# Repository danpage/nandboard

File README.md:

# NANDboard: hands-on Boolean algebra

<!--- -------------------------------------------------------------------- --->

## History

Starting in the 2012/13 academic year, the
[Computer Science Department](http://www.cs.bris.ac.uk)
at the
[University of Bristol](http://www.bris.ac.uk)
changed how the Undergraduate-level, 1st year (or "freshman") Computer
Architecture unit was delivered.  Although it *always* had a practical
emphasis, there was a view it should be even more hands-on.
There were various motivations, included the fact that
a) by doing so the topic could be more engaging,
   but also
b) it seeds an ethos and skills that are of general use: for example,
   it could mean students participate more actively in
   [maker-like](http://en.wikipedia.org/wiki/Maker_culture),
   hardware-based (versus software-only) projects.

The NANDboard, whose original concept and design was due to
[Simon Hollis](https://github.com/simonhollis),
was among various innovations introduced; Simon left at the end of the
2014/15 academic year, ~~prompting~~ forcing me to learn the basics of
PCB design and subsequently revise his initial NANDboard version.

<!--- -------------------------------------------------------------------- --->

## Concept

Although fundamentally important in Computer Science,
[Boolean algebra](http://en.wikipedia.org/wiki/Boolean_algebra)
is a notoriously dry topic.  The problem is exacerbated when hands-on 
experience amounts to solving paper-and-pencil exercises; the typical
result is for students to be increasingly uninterested and disengaged.
The underlying causes are varied, and differ from student to student.
However, anecdotally at least, the following are common:

- There is a disconnection between theory and practice, in the sense
  it is unclear how Boolean algebra directly relates to intuitively 
  useful forms of computation;
  this typically leads to students disengaging,
  based on the view that said theory has no practical use (to them).
- Paper-and-pencil exercises are of a necessarily small scale, which
  can mean 
  [toy problems](http://en.wikipedia.org/wiki/Toy_problem)
  dominate; 
  this typically leads to students disengaging, e.g., because they
  can easily solve said problems so avoid any deeper investigation
  of physical constraints and properties, and unusual designs
  (e.g., a [C-element](https://en.wikipedia.org/wiki/C-element)).
- In part due to the wealth of resources available, modern students 
  are used to and excited by the immediacy of software development;
  this is often direct motivation for studying Computer Science in 
  the first place, with Boolean algebra feeling like a regression 
  towards Mathematics (which, for some, is less popular).

Put another way, this approach is similar, by analogy, to learning
[C](http://en.wikipedia.org/wiki/C_(programming_language))
by studying the language and 
["hello world"](https://en.wikipedia.org/wiki/"Hello,_World!"_program)
style programs *without* ever actually compiling and executing them.

An obvious alternative is to connect theory and practice directly, by
supporting genuinely hands-on, experimental tasks.  One way to do so
might be to equip each student with a breadboard and some
[7400 series](https://en.wikipedia.org/wiki/List_of_7400_series_integrated_circuits)
ICs.  However, for us at least, this presented some problems:
a) large cohort sizes
   (of say 200+ students)
   make the logistics involved quite challenging,
b) said cohorts are typically unfamiliar with, and sometimes have an
   outright dislike for electronics.
The NANDboard attempts to manage these problems.  Conceptually, it is 
just a USB-powered breadboard pre-populated with NAND gates: it could
be viewed as a form of NAND-only
[PLA](http://en.wikipedia.org/wiki/Programmable_logic_array),
where implementation of a Boolean expression (cf. programming the PLA)
amounts to connecting pin headers (i.e., the gate inputs and outputs)
using jumper wire.  There are, of course, some gratuitous
[blinkenlights](http://en.wikipedia.org/wiki/Blinkenlights)
to visualise the inputs and outputs.

<!--- -------------------------------------------------------------------- --->

## Design

Motivated in part by observing how students use them, the NANDboard 
design has gone through several revisions as is illustrated below:

Revision | Image                                                                             | Design                                                                             |
:------: | :-------------------------------------------------------------------------------: | :--------------------------------------------------------------------------------: |
B        |  |                                                                                    |
C        |  |                                                                                    |
D        |  | [files](./rev_d), [schematic](./rev_d/README.pdf), [user guide](./rev_d/README.md) |
F        |  | [files](./rev_f), [schematic](./rev_f/README.pdf), [user guide](./rev_f/README.md) |

<!--- -------------------------------------------------------------------- --->

## Acknowledgements

Later revisions 
(e.g., rev. F) 
were designed and manufactured with generous support from 
[Elliptic Systems](https://elliptic-systems.com).

<!--- -------------------------------------------------------------------- --->

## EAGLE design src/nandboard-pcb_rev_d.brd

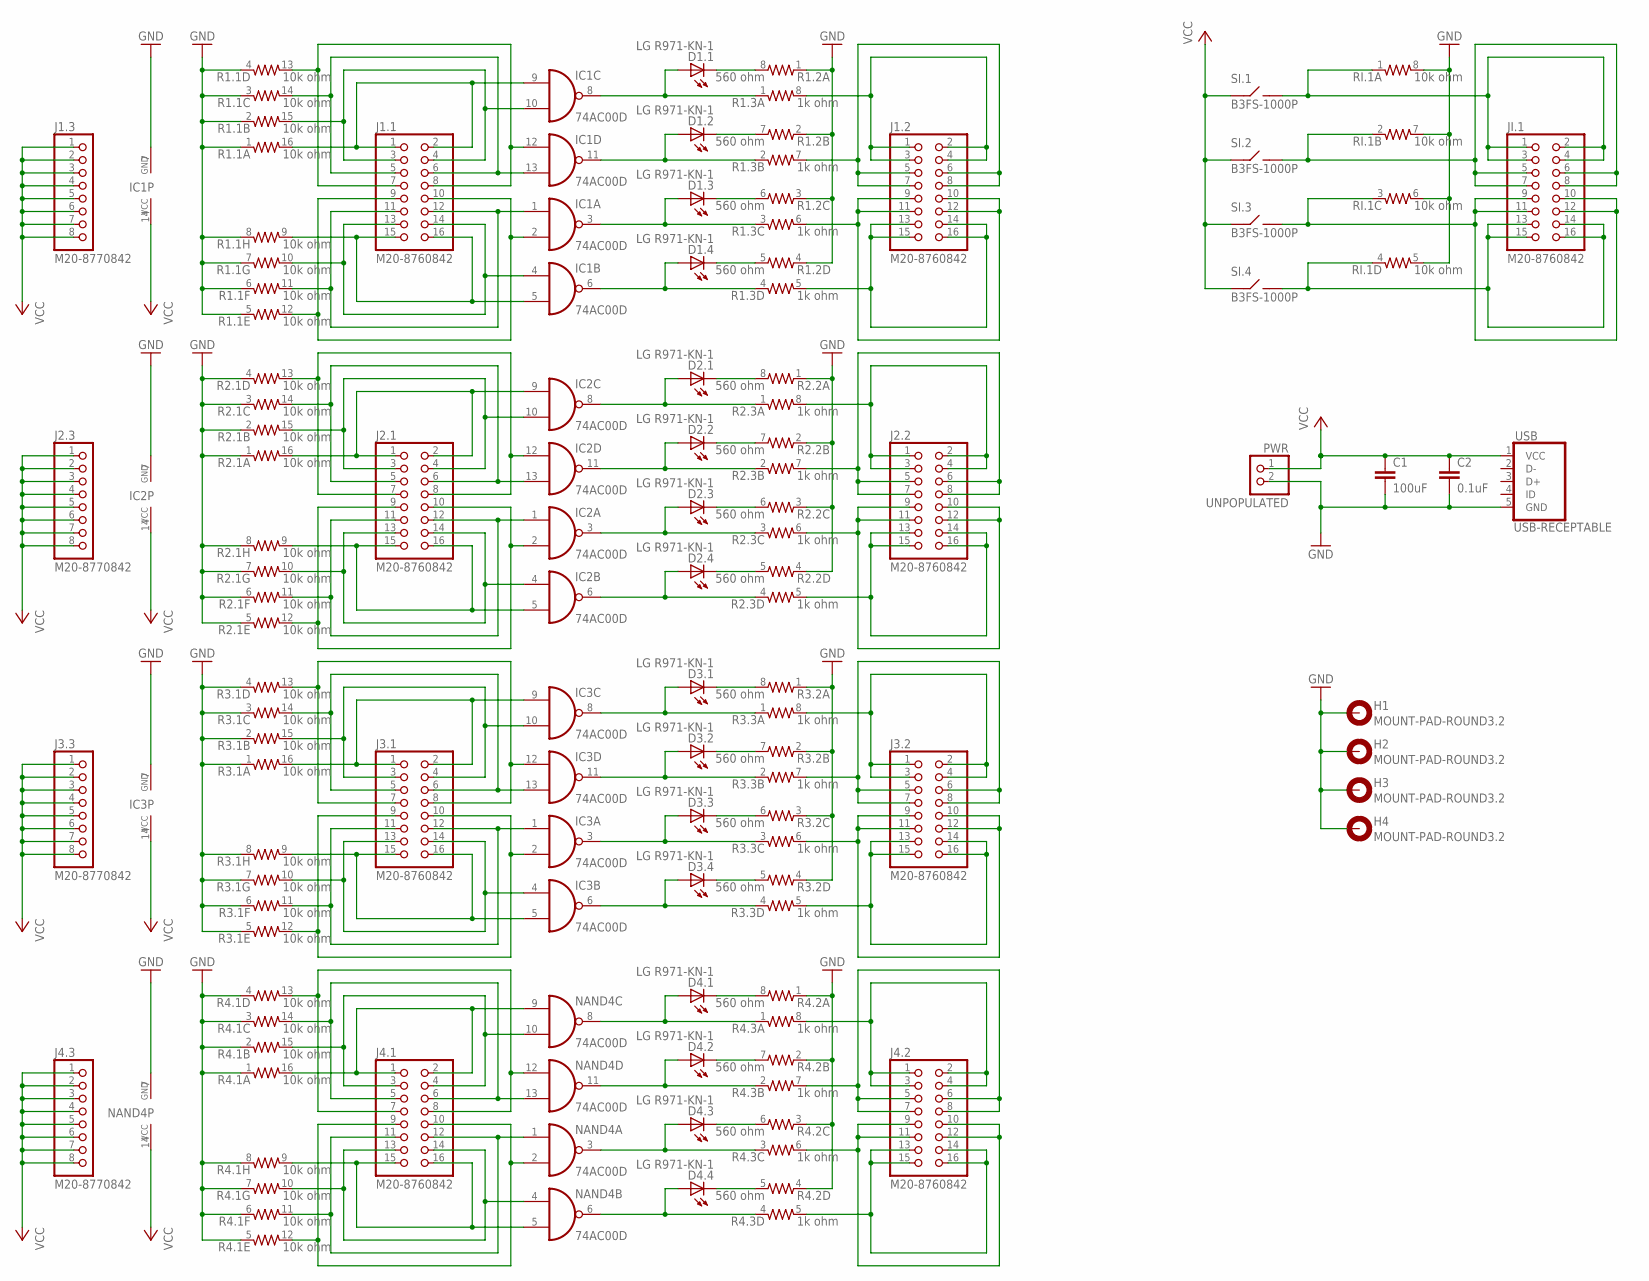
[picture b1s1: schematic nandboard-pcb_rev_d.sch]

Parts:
C1: 100uF; C1210
C2: 0.1uF; C0805
D1.1, D1.2, D1.3, D1.4, D2.1, D2.2, D2.3, D2.4, D3.1, D3.2, D3.3, D3.4, D4.1, D4.2, D4.3, D4.4: LG R971-KN-1; CHIPLED_0805
H1, H2, H3, H4: MOUNT-PAD-ROUND3.2; 3,2-PAD
IC1, IC2, IC3: 74AC00D; SO14
J1.1, J1.2, J2.1, J2.2, J3.1, J3.2, J4.1, J4.2: M20-8760842; 2X08_SMT
J1.3, J2.3, J3.3, J4.3: M20-8770842; 1X08_SMT
JI.1: M20-8760842; 2X08_SMT
NAND4: 74AC00D; SO14
PWR: UNPOPULATED; 1X02
R1.1, R2.1, R3.1, R4.1: 10k ohm; 742-16
R1.2, R2.2, R3.2, R4.2: 560 ohm; 742-8
R1.3, R2.3, R3.3, R4.3: 1k ohm; 742-8
RI.1: 10k ohm; 742-8
SI.1, SI.2, SI.3, SI.4: B3FS-1000P; B3FS-1000
USB: USB-RECEPTABLE; FCI-10103594-0001LF

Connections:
GND: C1.2, C2.2, H1.B3,2, H2.B3,2, H3.B3,2, H4.B3,2, IC1.7 (GND), IC2.7 (GND), IC3.7 (GND), NAND4.7 (GND), PWR.2, R1.1.1, R1.1.2 (1), R1.1.3 (1), R1.1.4 (1), R1.1.5 (1), R1.1.6 (1), R1.1.7 (1), R1.1.8 (1), R1.2.1, R1.2.2 (1), R1.2.3 (1), R1.2.4 (1), R2.1.1, R2.1.2 (1), R2.1.3 (1), R2.1.4 (1), R2.1.5 (1), R2.1.6 (1), R2.1.7 (1), R2.1.8 (1), R2.2.1, R2.2.2 (1), R2.2.3 (1), R2.2.4 (1), R3.1.1, R3.1.2 (1), R3.1.3 (1), R3.1.4 (1), R3.1.5 (1), R3.1.6 (1), R3.1.7 (1), R3.1.8 (1), R3.2.1, R3.2.2 (1), R3.2.3 (1), R3.2.4 (1), R4.1.1, R4.1.2 (1), R4.1.3 (1), R4.1.4 (1), R4.1.5 (1), R4.1.6 (1), R4.1.7 (1), R4.1.8 (1), R4.2.1, R4.2.2 (1), R4.2.3 (1), R4.2.4 (1), RI.1.5 (2), RI.1.6 (2), RI.1.7 (2), RI.1.8 (2), USB.5 (GND)
unnamed: IC2.9 (I0), J2.1.1, J2.1.2, R2.1.16 (2)
unnamed: IC2.10 (I1), J2.1.3, J2.1.4, R2.1.15 (2)
unnamed: JI.1.1, JI.1.2, JI.1.3, JI.1.4, RI.1.1, SI.1.3 (B), SI.1.4 (B)
unnamed: IC2.13 (I1), J2.1.5, J2.1.6, R2.1.14 (2)
unnamed: IC2.12 (I0), J2.1.7, J2.1.8, R2.1.13 (2)
unnamed: JI.1.5, JI.1.6, JI.1.7, JI.1.8, RI.1.2 (1), SI.2.3 (B), SI.2.4 (B)
unnamed: JI.1.9, JI.1.10, JI.1.11, JI.1.12, RI.1.3 (1), SI.3.3 (B), SI.3.4 (B)
unnamed: JI.1.13, JI.1.14, JI.1.15, JI.1.16, RI.1.4 (1), SI.4.3 (B), SI.4.4 (B)
unnamed: IC2.5 (I1), J2.1.15, J2.1.16, R2.1.9 (2)
unnamed: IC2.4 (I0), J2.1.13, J2.1.14, R2.1.10 (2)
unnamed: IC2.1 (I0), J2.1.11, J2.1.12, R2.1.11 (2)
unnamed: IC2.2 (I1), J2.1.9, J2.1.10, R2.1.12 (2)
unnamed: D1.4.C, R1.2.5 (2)
unnamed: D1.3.C, R1.2.6 (2)
unnamed: D1.2.C, R1.2.7 (2)
unnamed: D1.1.C, R1.2.8 (2)
unnamed: J2.2.13, J2.2.14, J2.2.15, J2.2.16, R2.3.5 (2)
unnamed: J2.2.9, J2.2.10, J2.2.11, J2.2.12, R2.3.6 (2)
unnamed: J2.2.1, J2.2.2, J2.2.3, J2.2.4, R2.3.8 (2)
unnamed: J2.2.5, J2.2.6, J2.2.7, J2.2.8, R2.3.7 (2)
unnamed: IC1.9 (I0), J1.1.1, J1.1.2, R1.1.16 (2)
unnamed: IC1.10 (I1), J1.1.3, J1.1.4, R1.1.15 (2)
unnamed: IC1.13 (I1), J1.1.5, J1.1.6, R1.1.14 (2)
unnamed: IC1.12 (I0), J1.1.7, J1.1.8, R1.1.13 (2)
unnamed: J1.2.13, J1.2.14, J1.2.15, J1.2.16, R1.3.5 (2)
unnamed: J1.2.9, J1.2.10, J1.2.11, J1.2.12, R1.3.6 (2)
unnamed: D1.1.A, IC1.8 (O), R1.3.1
unnamed: J1.2.1, J1.2.2, J1.2.3, J1.2.4, R1.3.8 (2)
unnamed: IC1.5 (I1), J1.1.15, J1.1.16, R1.1.9 (2)
unnamed: IC1.4 (I0), J1.1.13, J1.1.14, R1.1.10 (2)
unnamed: IC1.1 (I0), J1.1.11, J1.1.12, R1.1.11 (2)
unnamed: IC1.2 (I1), J1.1.9, J1.1.10, R1.1.12 (2)
unnamed: D1.2.A, IC1.11 (O), R1.3.2 (1)
unnamed: J1.2.5, J1.2.6, J1.2.7, J1.2.8, R1.3.7 (2)
unnamed: D1.3.A, IC1.3 (O), R1.3.3 (1)
unnamed: D1.4.A, IC1.6 (O), R1.3.4 (1)
unnamed: D2.1.A, IC2.8 (O), R2.3.1
unnamed: D2.2.A, IC2.11 (O), R2.3.2 (1)
unnamed: D2.3.A, IC2.3 (O), R2.3.3 (1)
unnamed: D2.4.A, IC2.6 (O), R2.3.4 (1)
unnamed: D2.1.C, R2.2.8 (2)
unnamed: D2.2.C, R2.2.7 (2)
unnamed: D2.3.C, R2.2.6 (2)
unnamed: D2.4.C, R2.2.5 (2)
unnamed: IC3.9 (I0), J3.1.1, J3.1.2, R3.1.16 (2)
unnamed: IC3.10 (I1), J3.1.3, J3.1.4, R3.1.15 (2)
unnamed: IC3.13 (I1), J3.1.5, J3.1.6, R3.1.14 (2)
unnamed: IC3.12 (I0), J3.1.7, J3.1.8, R3.1.13 (2)
unnamed: IC3.5 (I1), J3.1.15, J3.1.16, R3.1.9 (2)
unnamed: IC3.4 (I0), J3.1.13, J3.1.14, R3.1.10 (2)
unnamed: IC3.1 (I0), J3.1.11, J3.1.12, R3.1.11 (2)
unnamed: IC3.2 (I1), J3.1.9, J3.1.10, R3.1.12 (2)
unnamed: J3.2.13, J3.2.14, J3.2.15, J3.2.16, R3.3.5 (2)
unnamed: J3.2.9, J3.2.10, J3.2.11, J3.2.12, R3.3.6 (2)
unnamed: J3.2.1, J3.2.2, J3.2.3, J3.2.4, R3.3.8 (2)
unnamed: J3.2.5, J3.2.6, J3.2.7, J3.2.8, R3.3.7 (2)
unnamed: D3.1.A, IC3.8 (O), R3.3.1
unnamed: D3.2.A, IC3.11 (O), R3.3.2 (1)
unnamed: D3.3.A, IC3.3 (O), R3.3.3 (1)
unnamed: D3.4.A, IC3.6 (O), R3.3.4 (1)
unnamed: D3.4.C, R3.2.5 (2)
unnamed: D3.3.C, R3.2.6 (2)
unnamed: D3.2.C, R3.2.7 (2)
unnamed: D3.1.C, R3.2.8 (2)
unnamed: J4.1.1, J4.1.2, NAND4.9 (I0), R4.1.16 (2)
unnamed: J4.1.3, J4.1.4, NAND4.10 (I1), R4.1.15 (2)
unnamed: J4.1.5, J4.1.6, NAND4.13 (I1), R4.1.14 (2)
unnamed: J4.1.7, J4.1.8, NAND4.12 (I0), R4.1.13 (2)
unnamed: J4.1.15, J4.1.16, NAND4.5 (I1), R4.1.9 (2)
unnamed: J4.1.13, J4.1.14, NAND4.4 (I0), R4.1.10 (2)
unnamed: J4.1.11, J4.1.12, NAND4.1 (I0), R4.1.11 (2)
unnamed: J4.1.9, J4.1.10, NAND4.2 (I1), R4.1.12 (2)
unnamed: J4.2.13, J4.2.14, J4.2.15, J4.2.16, R4.3.5 (2)
unnamed: J4.2.9, J4.2.10, J4.2.11, J4.2.12, R4.3.6 (2)
unnamed: J4.2.1, J4.2.2, J4.2.3, J4.2.4, R4.3.8 (2)
unnamed: J4.2.5, J4.2.6, J4.2.7, J4.2.8, R4.3.7 (2)
unnamed: D4.1.A, NAND4.8 (O), R4.3.1
unnamed: D4.2.A, NAND4.11 (O), R4.3.2 (1)
unnamed: D4.3.A, NAND4.3 (O), R4.3.3 (1)
unnamed: D4.4.A, NAND4.6 (O), R4.3.4 (1)
unnamed: D4.1.C, R4.2.8 (2)
unnamed: D4.2.C, R4.2.7 (2)
unnamed: D4.3.C, R4.2.6 (2)
unnamed: D4.4.C, R4.2.5 (2)
VCC: C1.1, C2.1, IC1.14 (VCC), IC2.14 (VCC), IC3.14 (VCC), J1.3.1, J1.3.2, J1.3.3, J1.3.4, J1.3.5, J1.3.6, J1.3.7, J1.3.8, J2.3.1, J2.3.2, J2.3.3, J2.3.4, J2.3.5, J2.3.6, J2.3.7, J2.3.8, J3.3.1, J3.3.2, J3.3.3, J3.3.4, J3.3.5, J3.3.6, J3.3.7, J3.3.8, J4.3.1, J4.3.2, J4.3.3, J4.3.4, J4.3.5, J4.3.6, J4.3.7, J4.3.8, NAND4.14 (VCC), PWR.1, SI.1.1 (A), SI.1.2 (A), SI.2.1 (A), SI.2.2 (A), SI.3.1 (A), SI.3.2 (A), SI.4.1 (A), SI.4.2 (A), USB.1 (VCC)

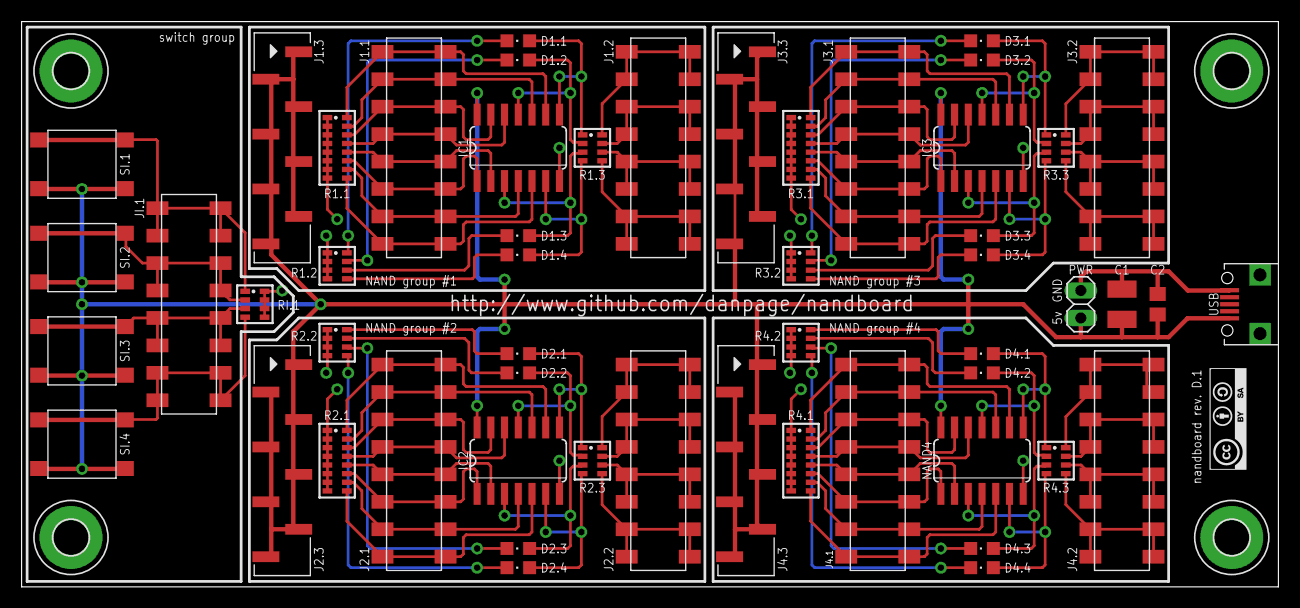
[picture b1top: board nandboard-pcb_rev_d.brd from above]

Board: 2 copper layers, 116.3 x 52.3 mm, 58 parts (0 on the bottom side), 86 nets.

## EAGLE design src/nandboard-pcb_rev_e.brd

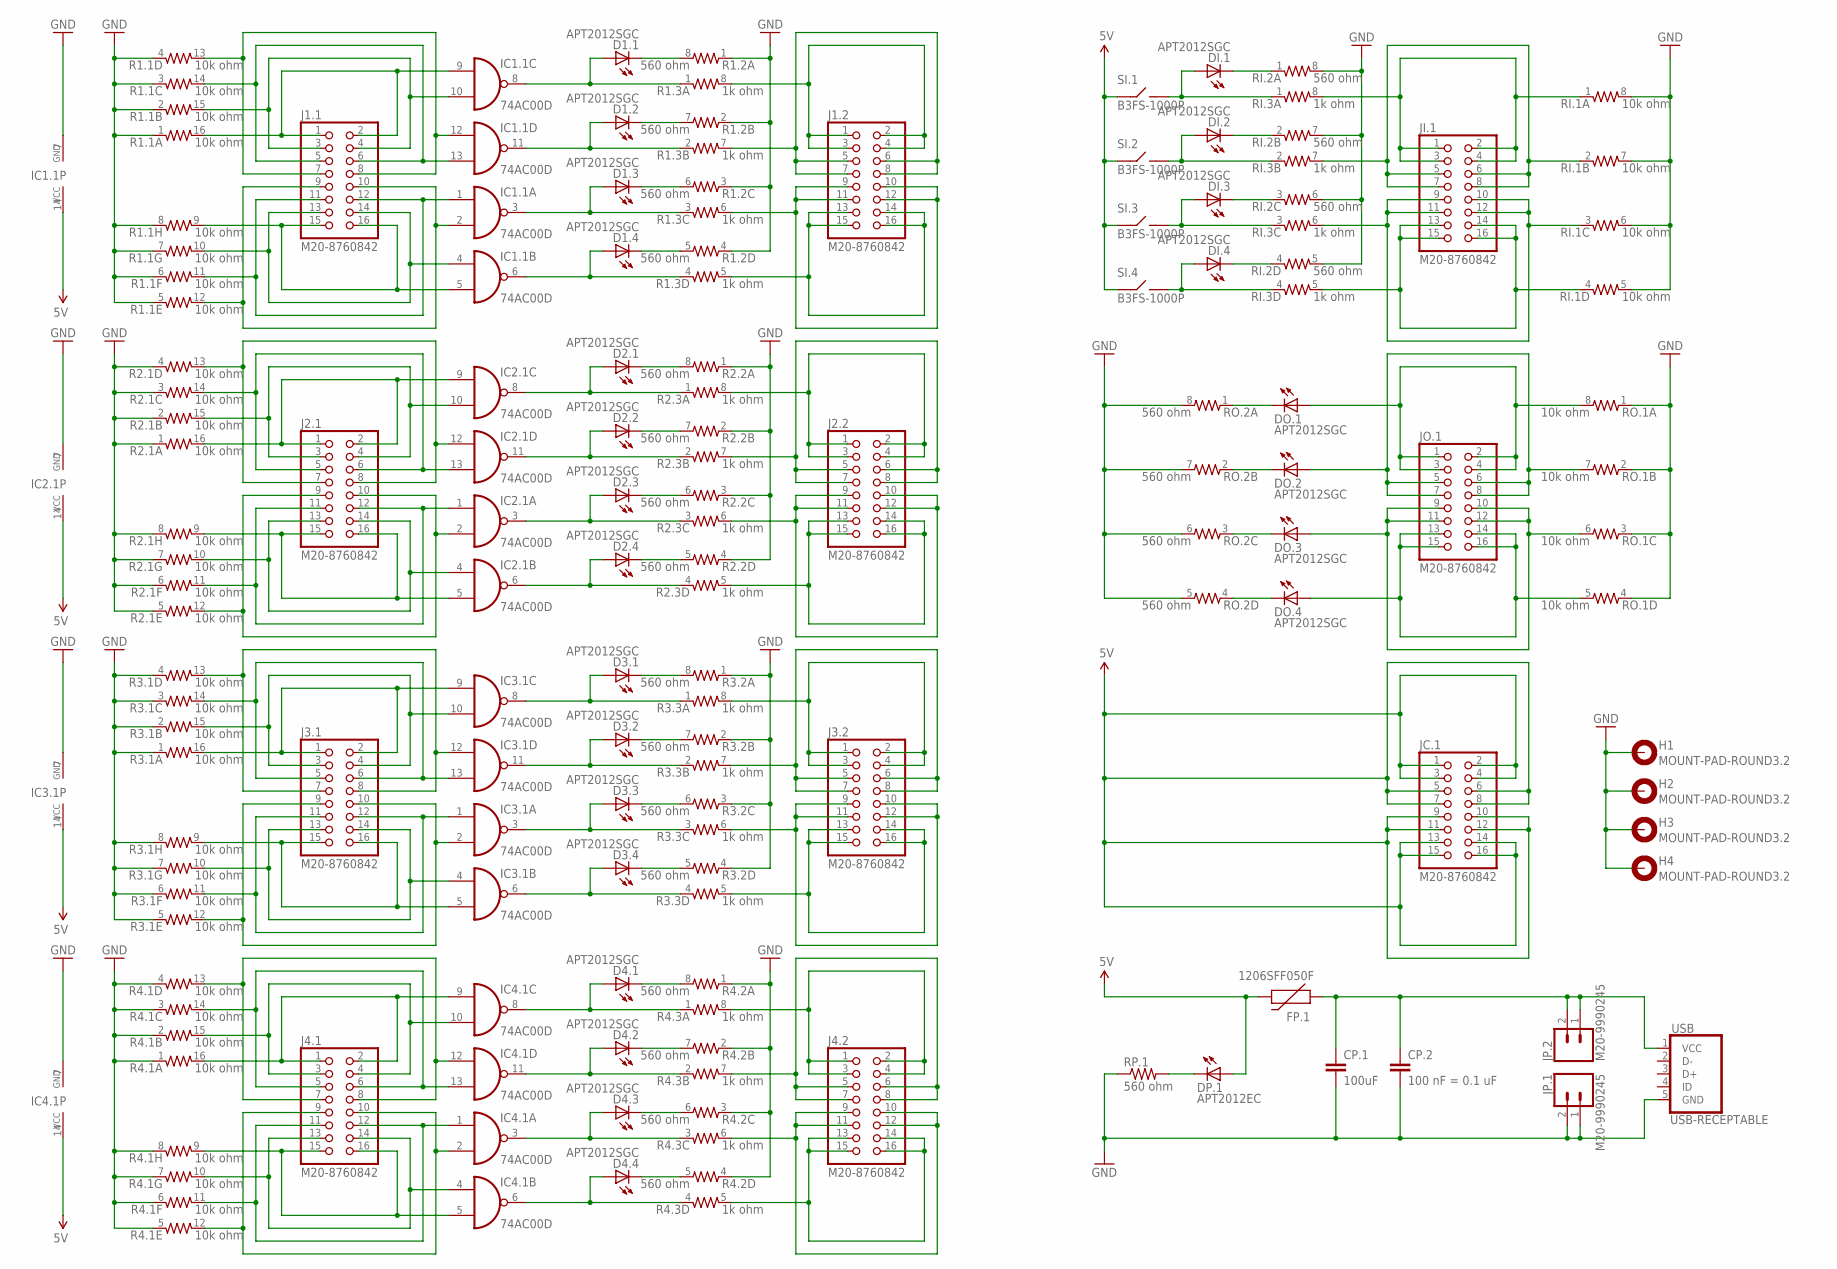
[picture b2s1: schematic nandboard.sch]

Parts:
CP.1: 100uF; C1210
CP.2: 100 nF = 0.1 uF; C0805
D1.1, D1.2, D1.3, D1.4, D2.1, D2.2, D2.3, D2.4, D3.1, D3.2, D3.3, D3.4, D4.1, D4.2, D4.3, D4.4: APT2012SGC; CHIPLED_0805
DI.1, DI.2, DI.3, DI.4: APT2012SGC; CHIPLED_0805
DO.1, DO.2, DO.3, DO.4: APT2012SGC; CHIPLED_0805
DP.1: APT2012EC; CHIPLED_0805
FP.1: 1206SFF050F; PTC-1206
H1, H2, H3, H4: MOUNT-PAD-ROUND3.2; 3,2-PAD
IC1.1, IC2.1, IC3.1, IC4.1: 74AC00D; SO14
J1.1, J1.2, J2.1, J2.2, J3.1, J3.2, J4.1, J4.2: M20-8760842; 2X08_SMT
JC.1: M20-8760842; 2X08_SMT
JI.1: M20-8760842; 2X08_SMT
JO.1: M20-8760842; 2X08_SMT
JP.1, JP.2: M20-9990245; 1X02
R1.1, R2.1, R3.1, R4.1: 10k ohm; 742-16
R1.2, R2.2, R3.2, R4.2: 560 ohm; 742-8
R1.3, R2.3, R3.3, R4.3: 1k ohm; 742-8
RI.1: 10k ohm; 742-8
RI.2: 560 ohm; 742-8
RI.3: 1k ohm; 742-8
RO.1: 10k ohm; 742-8
RO.2: 560 ohm; 742-8
RP.1: 560 ohm; R0603
SI.1, SI.2, SI.3, SI.4: B3FS-1000P; B3FS-1000
USB: USB-RECEPTABLE; FCI-10103594-0001LF

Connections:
5V: DP.1.A, FP.1.2, IC1.1.14 (VCC), IC2.1.14 (VCC), IC3.1.14 (VCC), IC4.1.14 (VCC), JC.1.1, JC.1.2, JC.1.3, JC.1.4, JC.1.5, JC.1.6, JC.1.7, JC.1.8, JC.1.9, JC.1.10, JC.1.11, JC.1.12, JC.1.13, JC.1.14, JC.1.15, JC.1.16, SI.1.1 (A), SI.1.2 (A), SI.2.1 (A), SI.2.2 (A), SI.3.1 (A), SI.3.2 (A), SI.4.1 (A), SI.4.2 (A)
GND: CP.1.2, CP.2.2, H1.B3,2, H2.B3,2, H3.B3,2, H4.B3,2, IC1.1.7 (GND), IC2.1.7 (GND), IC3.1.7 (GND), IC4.1.7 (GND), JP.1.1, JP.1.2, R1.1.1, R1.1.2 (1), R1.1.3 (1), R1.1.4 (1), R1.1.5 (1), R1.1.6 (1), R1.1.7 (1), R1.1.8 (1), R1.2.1, R1.2.2 (1), R1.2.3 (1), R1.2.4 (1), R2.1.1, R2.1.2 (1), R2.1.3 (1), R2.1.4 (1), R2.1.5 (1), R2.1.6 (1), R2.1.7 (1), R2.1.8 (1), R2.2.1, R2.2.2 (1), R2.2.3 (1), R2.2.4 (1), R3.1.1, R3.1.2 (1), R3.1.3 (1), R3.1.4 (1), R3.1.5 (1), R3.1.6 (1), R3.1.7 (1), R3.1.8 (1), R3.2.1, R3.2.2 (1), R3.2.3 (1), R3.2.4 (1), R4.1.1, R4.1.2 (1), R4.1.3 (1), R4.1.4 (1), R4.1.5 (1), R4.1.6 (1), R4.1.7 (1), R4.1.8 (1), R4.2.1, R4.2.2 (1), R4.2.3 (1), R4.2.4 (1), RI.1.5 (2), RI.1.6 (2), RI.1.7 (2), RI.1.8 (2), RI.2.5 (2), RI.2.6 (2), RI.2.7 (2), RI.2.8 (2), RO.1.1, RO.1.2 (1), RO.1.3 (1), RO.1.4 (1), RO.2.5 (2), RO.2.6 (2), RO.2.7 (2), RO.2.8 (2), RP.1.1, USB.5 (GND)
unnamed: IC2.1.9 (I0), J2.1.1, J2.1.2, R2.1.16 (2)
unnamed: IC2.1.10 (I1), J2.1.3, J2.1.4, R2.1.15 (2)
unnamed: JI.1.1, JI.1.2, JI.1.3, JI.1.4, RI.1.1, RI.3.8 (2)
unnamed: IC2.1.13 (I1), J2.1.5, J2.1.6, R2.1.14 (2)
unnamed: IC2.1.12 (I0), J2.1.7, J2.1.8, R2.1.13 (2)
unnamed: JI.1.5, JI.1.6, JI.1.7, JI.1.8, RI.1.2 (1), RI.3.7 (2)
unnamed: JI.1.9, JI.1.10, JI.1.11, JI.1.12, RI.1.3 (1), RI.3.6 (2)
unnamed: JI.1.13, JI.1.14, JI.1.15, JI.1.16, RI.1.4 (1), RI.3.5 (2)
unnamed: IC2.1.5 (I1), J2.1.15, J2.1.16, R2.1.9 (2)
unnamed: IC2.1.4 (I0), J2.1.13, J2.1.14, R2.1.10 (2)
unnamed: IC2.1.1 (I0), J2.1.11, J2.1.12, R2.1.11 (2)
unnamed: IC2.1.2 (I1), J2.1.9, J2.1.10, R2.1.12 (2)
unnamed: D1.4.C, R1.2.5 (2)
unnamed: D2.1.C, R2.2.8 (2)
unnamed: D2.2.C, R2.2.7 (2)
unnamed: D1.2.C, R1.2.7 (2)
unnamed: J2.2.13, J2.2.14, J2.2.15, J2.2.16, R2.3.5 (2)
unnamed: J2.2.9, J2.2.10, J2.2.11, J2.2.12, R2.3.6 (2)
unnamed: J2.2.1, J2.2.2, J2.2.3, J2.2.4, R2.3.8 (2)
unnamed: J2.2.5, J2.2.6, J2.2.7, J2.2.8, R2.3.7 (2)
unnamed: IC1.1.9 (I0), J1.1.1, J1.1.2, R1.1.16 (2)
unnamed: IC1.1.10 (I1), J1.1.3, J1.1.4, R1.1.15 (2)
unnamed: IC1.1.13 (I1), J1.1.5, J1.1.6, R1.1.14 (2)
unnamed: IC1.1.12 (I0), J1.1.7, J1.1.8, R1.1.13 (2)
unnamed: J1.2.13, J1.2.14, J1.2.15, J1.2.16, R1.3.5 (2)
unnamed: J1.2.9, J1.2.10, J1.2.11, J1.2.12, R1.3.6 (2)
unnamed: D1.1.A, IC1.1.8 (O), R1.3.1
unnamed: J1.2.1, J1.2.2, J1.2.3, J1.2.4, R1.3.8 (2)
unnamed: IC1.1.5 (I1), J1.1.15, J1.1.16, R1.1.9 (2)
unnamed: IC1.1.4 (I0), J1.1.13, J1.1.14, R1.1.10 (2)
unnamed: IC1.1.1 (I0), J1.1.11, J1.1.12, R1.1.11 (2)
unnamed: IC1.1.2 (I1), J1.1.9, J1.1.10, R1.1.12 (2)
unnamed: D1.2.A, IC1.1.11 (O), R1.3.2 (1)
unnamed: J1.2.5, J1.2.6, J1.2.7, J1.2.8, R1.3.7 (2)
unnamed: D1.3.A, IC1.1.3 (O), R1.3.3 (1)
unnamed: D1.4.A, IC1.1.6 (O), R1.3.4 (1)
unnamed: D2.1.A, IC2.1.8 (O), R2.3.1
unnamed: D2.2.A, IC2.1.11 (O), R2.3.2 (1)
unnamed: D2.3.A, IC2.1.3 (O), R2.3.3 (1)
unnamed: D2.4.A, IC2.1.6 (O), R2.3.4 (1)
unnamed: D1.1.C, R1.2.8 (2)
unnamed: D1.3.C, R1.2.6 (2)
unnamed: D2.3.C, R2.2.6 (2)
unnamed: D2.4.C, R2.2.5 (2)
unnamed: IC3.1.9 (I0), J3.1.1, J3.1.2, R3.1.16 (2)
unnamed: IC3.1.10 (I1), J3.1.3, J3.1.4, R3.1.15 (2)
unnamed: IC3.1.13 (I1), J3.1.5, J3.1.6, R3.1.14 (2)
unnamed: IC3.1.12 (I0), J3.1.7, J3.1.8, R3.1.13 (2)
unnamed: IC3.1.5 (I1), J3.1.15, J3.1.16, R3.1.9 (2)
unnamed: IC3.1.4 (I0), J3.1.13, J3.1.14, R3.1.10 (2)
unnamed: IC3.1.1 (I0), J3.1.11, J3.1.12, R3.1.11 (2)
unnamed: IC3.1.2 (I1), J3.1.9, J3.1.10, R3.1.12 (2)
unnamed: J3.2.13, J3.2.14, J3.2.15, J3.2.16, R3.3.5 (2)
unnamed: J3.2.9, J3.2.10, J3.2.11, J3.2.12, R3.3.6 (2)
unnamed: J3.2.1, J3.2.2, J3.2.3, J3.2.4, R3.3.8 (2)
unnamed: J3.2.5, J3.2.6, J3.2.7, J3.2.8, R3.3.7 (2)
unnamed: D3.1.A, IC3.1.8 (O), R3.3.1
unnamed: D3.2.A, IC3.1.11 (O), R3.3.2 (1)
unnamed: D3.3.A, IC3.1.3 (O), R3.3.3 (1)
unnamed: D3.4.A, IC3.1.6 (O), R3.3.4 (1)
unnamed: D3.4.C, R3.2.5 (2)
unnamed: D3.3.C, R3.2.6 (2)
unnamed: D3.2.C, R3.2.7 (2)
unnamed: D3.1.C, R3.2.8 (2)
unnamed: IC4.1.9 (I0), J4.1.1, J4.1.2, R4.1.16 (2)
unnamed: IC4.1.10 (I1), J4.1.3, J4.1.4, R4.1.15 (2)
unnamed: IC4.1.13 (I1), J4.1.5, J4.1.6, R4.1.14 (2)
unnamed: IC4.1.12 (I0), J4.1.7, J4.1.8, R4.1.13 (2)
unnamed: IC4.1.5 (I1), J4.1.15, J4.1.16, R4.1.9 (2)
unnamed: IC4.1.4 (I0), J4.1.13, J4.1.14, R4.1.10 (2)
unnamed: IC4.1.1 (I0), J4.1.11, J4.1.12, R4.1.11 (2)
unnamed: IC4.1.2 (I1), J4.1.9, J4.1.10, R4.1.12 (2)
unnamed: J4.2.13, J4.2.14, J4.2.15, J4.2.16, R4.3.5 (2)
unnamed: J4.2.9, J4.2.10, J4.2.11, J4.2.12, R4.3.6 (2)
unnamed: J4.2.1, J4.2.2, J4.2.3, J4.2.4, R4.3.8 (2)
unnamed: J4.2.5, J4.2.6, J4.2.7, J4.2.8, R4.3.7 (2)
unnamed: D4.1.A, IC4.1.8 (O), R4.3.1
unnamed: D4.2.A, IC4.1.11 (O), R4.3.2 (1)
unnamed: D4.3.A, IC4.1.3 (O), R4.3.3 (1)
unnamed: D4.4.A, IC4.1.6 (O), R4.3.4 (1)
unnamed: D4.1.C, R4.2.8 (2)
unnamed: D4.2.C, R4.2.7 (2)
unnamed: D4.3.C, R4.2.6 (2)
unnamed: D4.4.C, R4.2.5 (2)
unnamed: DO.1.C, RO.2.1
unnamed: DO.2.C, RO.2.2 (1)
unnamed: DO.3.C, RO.2.3 (1)
unnamed: DO.4.C, RO.2.4 (1)
unnamed: DO.1.A, JO.1.1, JO.1.2, JO.1.3, JO.1.4, RO.1.8 (2)
unnamed: DO.2.A, JO.1.5, JO.1.6, JO.1.7, JO.1.8, RO.1.7 (2)
unnamed: DO.3.A, JO.1.9, JO.1.10, JO.1.11, JO.1.12, RO.1.6 (2)
unnamed: DO.4.A, JO.1.13, JO.1.14, JO.1.15, JO.1.16, RO.1.5 (2)
unnamed: CP.1.1, CP.2.1, FP.1.1, JP.2.1, JP.2.2, USB.1 (VCC)
unnamed: DI.2.A, RI.3.2 (1), SI.2.3 (B), SI.2.4 (B)
unnamed: DI.3.A, RI.3.3 (1), SI.3.3 (B), SI.3.4 (B)
unnamed: DI.1.A, RI.3.1, SI.1.3 (B), SI.1.4 (B)
unnamed: DI.4.A, RI.3.4 (1), SI.4.3 (B), SI.4.4 (B)
unnamed: DI.1.C, RI.2.1
unnamed: DI.2.C, RI.2.2 (1)
unnamed: DI.3.C, RI.2.3 (1)
unnamed: DI.4.C, RI.2.4 (1)
unnamed: DP.1.C, RP.1.2

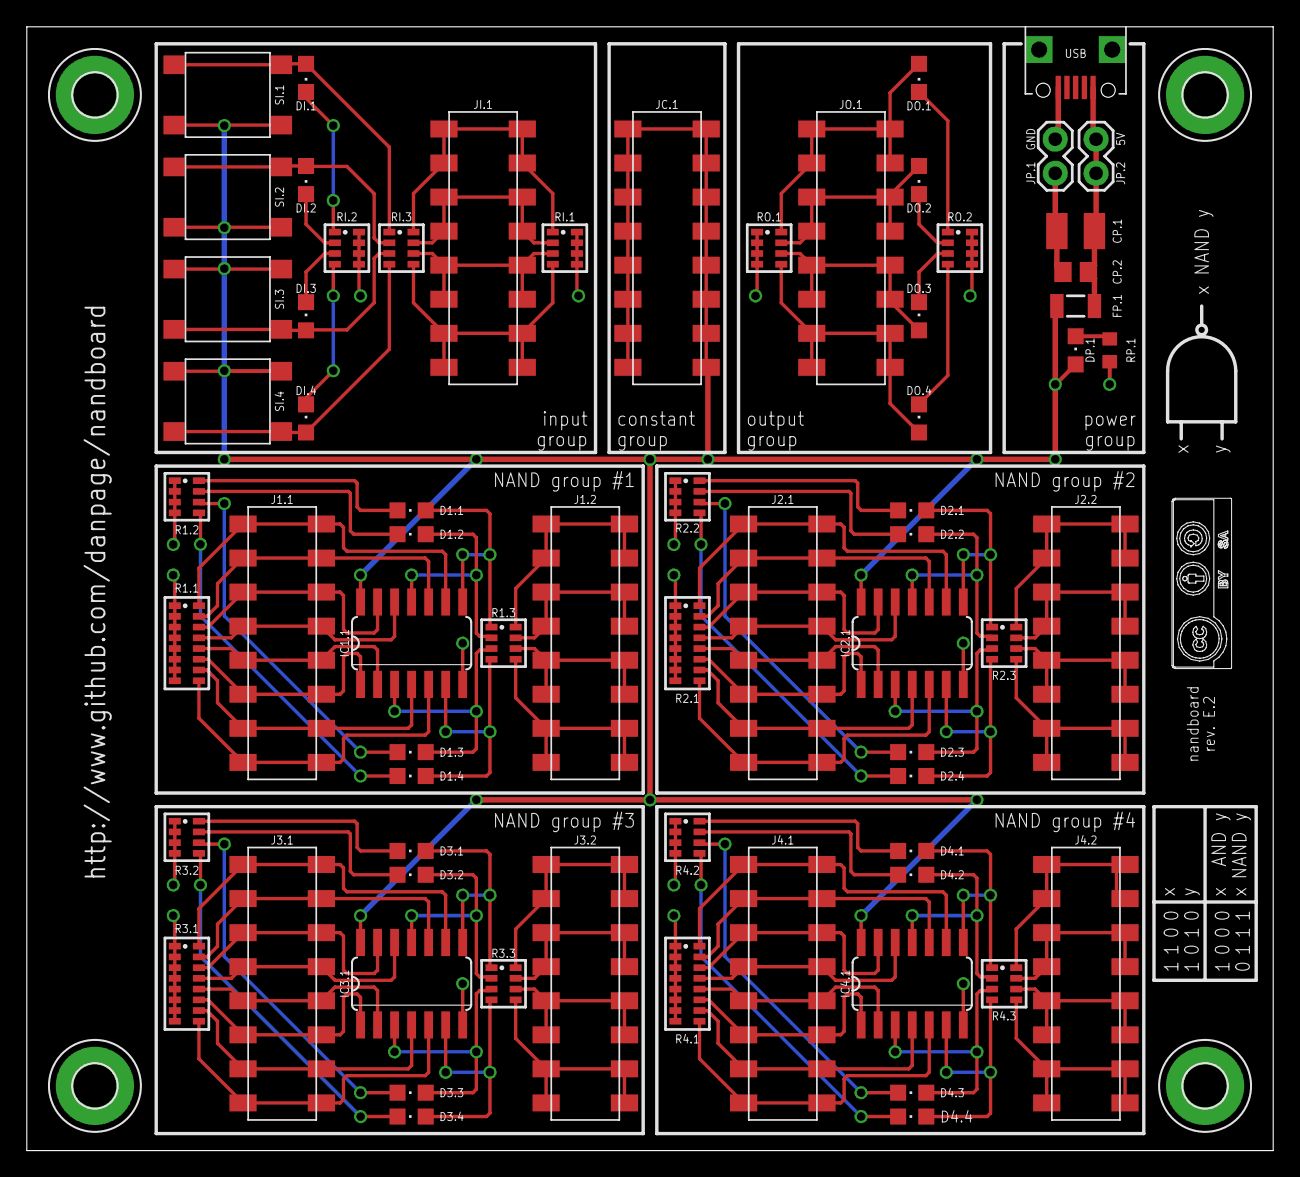
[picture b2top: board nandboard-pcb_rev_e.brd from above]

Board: 2 copper layers, 93.0 x 83.8 mm, 72 parts (0 on the bottom side), 104 nets.

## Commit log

2015-10-05 initial commit of rev. D design, plus fleshed out README.txt etc.
2017-04-12 updated to rev. E design, moved to Octopart-based BOM, improved README.md
2017-04-12 clean-up of older files
2017-04-13 fixed a couple of markdown glitches
2017-07-06 updated README.md to include OSH Park PCB link
2017-07-20 added CSV-based BOMs (replicating Octopart BOM offline)
2017-08-16 reorganised design files; improved photography a little
2017-08-16 fixed typo. in image path
2018-05-31 fixed typos in URLs; added schematic PDFs
2018-05-31 move PDFs to LFS-based storage
2021-11-09 Update README.md
    https://forum.kicad.info/t/warning-avoid-all-links-to-kicad-pcb-org-use-kicad-org/31521
2024-09-02 start work on content for rev_f
2024-09-09 bump
2024-09-13 add rev. F; remove rev. E; restructure user guide(s); rewrite PDF generator(s)
2024-09-20 update PCB photo with better version
2025-01-07 update URL for Simon from (dead) CS -> GitHub

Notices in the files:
parts and their libraries:
resistor-array: Copyright (C) 2008, Bob Starr
SparkFun-Aesthetics: Licensing: Creative Commons ShareAlike 4.0 International - https://creativecommons.org/licenses/by-sa/4.0
